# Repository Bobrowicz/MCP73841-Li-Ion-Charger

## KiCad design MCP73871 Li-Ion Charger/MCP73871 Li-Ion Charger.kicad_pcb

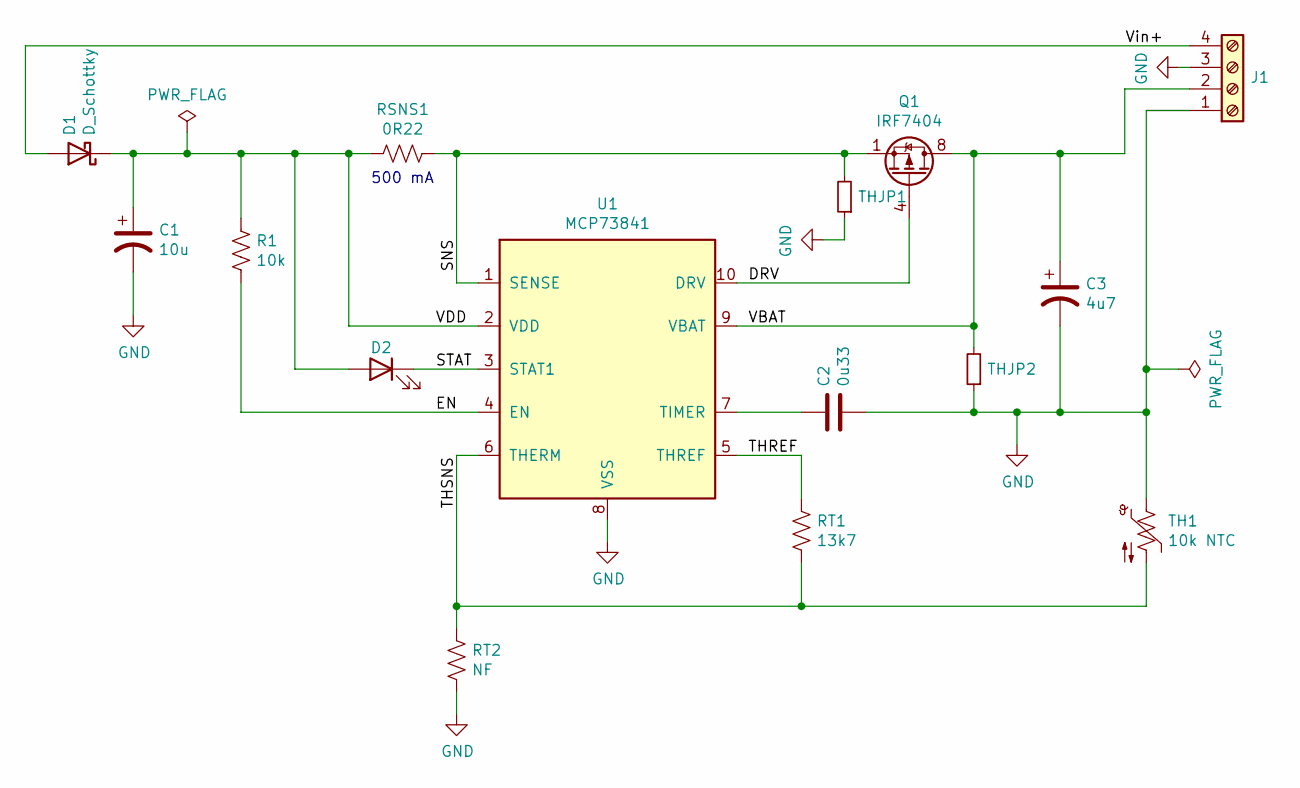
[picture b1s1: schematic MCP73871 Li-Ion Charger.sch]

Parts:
C1: 10u; CP_Radial_D5.0mm_P2.00mm
C2: 0u33; C_0805_HandSoldering
C3: 4u7; CP_Radial_D5.0mm_P2.00mm
D1: D_Schottky; D_SMA_Handsoldering
D2: LED; D_0805
J1: Screw_Terminal_01x04; CUI_TB007-508-04BE
Q1: IRF7404; SOIC-8_3.9x4.9mm_Pitch1.27mm
R1: 10k; R_0805_HandSoldering
RSNS1: 0R22; R_0805_HandSoldering
RT1: 13k7; R_0805_HandSoldering
RT2: NF; R_0805_HandSoldering
TH1: 10k NTC; Socket_Strip_Straight_1x02_Pitch2.54mm
THJP1, THJP2: TH JMP; R_1206_HandSoldering
U1: MCP73841; MSOP-10_3x3mm_Pitch0.5mm

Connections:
/DRV: Q1.4 (G), U1.10 (DRV)
/EN: R1.1, U1.4 (EN)
/SNS: Q1.1 (S), Q1.2 (S), Q1.3 (S), RSNS1.1, THJP1.2, U1.1 (SENSE)
/STAT: D2.1 (K), U1.3 (STAT1)
/THREF: RT1.1, U1.5 (THREF)
/THSNS: RT1.2, RT2.1, TH1.2, U1.6 (THERM)
/VBAT: C3.1, J1.2, Q1.5 (D), Q1.6 (D), Q1.7 (D), Q1.8 (D), THJP2.2, U1.9 (VBAT)
/VDD: C1.1, D1.1 (K), D2.2 (A), R1.2, RSNS1.2, U1.2 (VDD)
/Vin+: D1.2 (A), J1.4
GND: C1.2, C2.2, C3.2, J1.1, J1.3, RT2.2, TH1.1, THJP1.1, THJP2.1, U1.8 (VSS)
unnamed: C2.1, U1.7 (TIMER)

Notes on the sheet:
500 mA

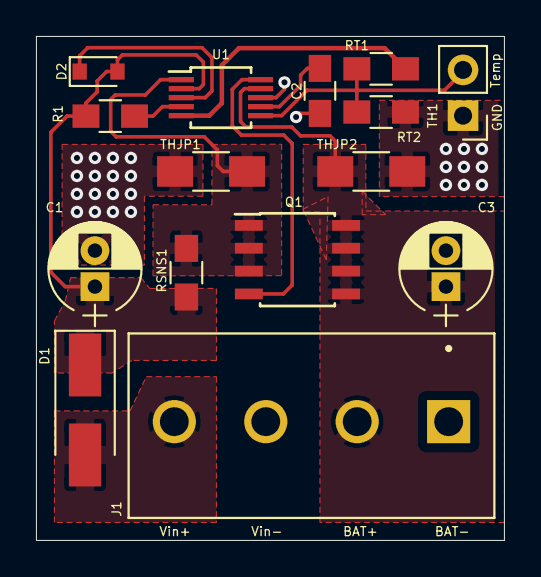
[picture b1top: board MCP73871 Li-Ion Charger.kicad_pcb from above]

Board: 2 copper layers, 26.0 x 28.0 mm, 15 parts (0 on the bottom side), 11 nets.
